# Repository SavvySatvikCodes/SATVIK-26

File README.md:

# SATVIK-26

**A custom STM32H743 flight controller, designed from scratch for ArduPilot.**

36 × 36 mm, 30.5 mm stack mounting, 4-layer. My first PCB, built for Hack Club Macondo.

---
## What this is

SATVIK-26 is a flight controller: the computer that reads a drone's sensors and decides how fast to spin each motor. It runs [ArduPilot](https://ardupilot.org/) on an STM32H743VIT6, a 480 MHz Cortex-M7.

Anyone can just buy a flight controller and assemble a drone, but I wanted to understand one. There is a large gap between knowing that an IMU talks over Serial Peripheral Interface contrast to having placed that IMU's decoupling capacitor yourself, knowing why it sits exactly where it sits. The only way I know to cross that gap is to draw the schematic and route the board.

This repo is the complete hardware design: schematic, layout, gerbers, BOM, and the reasoning behind the decisions.

---
## Specifications

- MCU - STM32H743VIT6, LQFP-100, 480 MHz Cortex-M7, 2 MB flash/1 MB RAM
- IMU	- ICM-42688-P (TDK InvenSense), SPI1
- Barometer - BMP388 (Bosch), I2C2
- Storage - microSD on SDMMC1 for onboard logging
- USB-C with USBLC6-2SC6 ESD protection, DFU accessible
- Input - 2 to 6S direct battery, SMBJ26A TVS clamp
- 5 V rail - TPS54560 buck, 15 µH inductor, SS56 catch diode
- 3.3 V rail - AP2112K-3.3 LDO from the 5 V rail
- Sensing - VBAT divider and ESC current sense into ADC1
- Motor outputs - 8 PWM channels
- Serial - 6 UARTs on JST-GH connectors
- Board - 36 × 36 mm, 4-layer FR4, 1.6 mm, 3 mm corner radius
- Mounting - 4 × M3 at 30.5 mm (standard FC stack)
- Components - 80 footprints, 55 top and 25 bottom
- Weight - 40 g

---
## What makes this not a copy

**Dual airframe, 8 PWM outputs.** Most 5-inch quad boards break out four motor outputs. I mapped eight timer channels to headers so the same board can fly a quad now and a fixed-wing later, where you need servo channels for ailerons, elevator and rudder on top of throttle. Four outputs would have made this a dead end. Eight cost me real routing space on a 36 mm board, and I decided the flexibility was worth it.

**FPV designed in, not bolted on.** A dedicated UART is broken out for a video transmitter, and the 5 V rail is sized with headroom to feed a camera and VTX rather than just flight electronics. Retrofitting FPV onto a board that never planned for it means splicing into power and hunting for a spare serial port.

**A custom ArduPilot hwdef.** ArduPilot does not know what is wired where on a board it has never seen. I am writing a `hwdef.dat` describing every peripheral, pin function and timer assignment, and the build system compiles firmware specifically for your hardware. That port is part of this project. The board is not finished until it boots real firmware.

For the record: Macondo's flight controller guide builds a **rocket** FC on a different MCU with a battery charger IC. This is a drone FC on an H7, no charger, different power tree, different sensors.

---
## Design decisions

- **TPS54560 buck, rated to 60V.** On 4S that looks like overkill, and cheaper 28 V parts would work. I took the headroom deliberately. 6S is 25.2 V charged, uncomfortably close to a 28 V absolute maximum, and a motor decelerating hard dumps energy back into the rail.
- **Entire power section moved to the back.** I could not route the board with everything on top. Rather than grow it to 40 × 40 and lose stack compatibility, the buck, inductor, LDO, filter caps and thirteen control passives all went to the bottom. That freed the top for MCU fanout, and it put the noisiest thing on the board on the opposite side of a solid ground plane from the IMU, crystal and USB pair. A space fix that turned out to be the right electrical call.
- **IMU as close to the mounting centroid as possible.** The further a sensor sits from the centre of rotation, the more frame vibration it reads as acceleration that is not real. Vibration is the most common cause of bad behaviour in custom ArduPilot builds.
- **Lower KV motors chosen on purpose.** 1855 KV instead of the common 2400 KV. Lower prop RPM means less vibration reaching an IMU sitting on a board I designed myself with no proven mounting. It is also more efficient, which buys flight time. 2400 KV would give roughly 9:1 thrust-to-weight, which is race-quad territory and pointless for a GPS platform flying Loiter and Auto. It also makes tuning the IMU harder.

---
## Stackup
Four layers: **F.Cu** signal, **In1.Cu** GND plane, **In2.Cu** +3V3 plane, **B.Cu** signal and power section.

+3V3 touches 38 pads spread across the whole board. The net that is everywhere gets the plane. VBAT_RAW became short traces, which is all a local 8-pad net needs.

---
## The work

The tidy version above is not how it felt.
Placing components looks like the easy part. It is not. Almost anything fits on a board if all you care about is fitting. I built layouts that passed every clearance check and were physically impossible to route, with pads jammed against the board edge and no path out at all. Each one had to be scrapped and rebuilt.

The final routing push ran **18 hours straight, 1pm on July 22nd to 6am on July 23rd, without a break.** By the end: 1114 track segments, 89 vias, zero unconnected pads.

Some NotSoFun blunders:
- The IMU had been deleted from the board entirely, and I had not noticed
- The crystal had been deleted too
- Thirteen buck and LDO support components stranded on the wrong side after the power flip, meaning a switching regulator's feedback network would have had to via across the board
- A netclass rule silently matching nothing, so every "power" trace was drawing at 0.2 mm instead of 0.6 mm

AND YES... after so much work it is quite nail-biting to put it on JLCPCB to see if your work actually computes... the real test is still far off 

---

## Things I got wrong

- **Connector pin order.** My connectors run 5V, GND, TX, RX. Most off-the-shelf GPS modules and telemetry radios use Pixhawk order with ground on the _last_ pin. Stock cables do not line up, and plugging one in without checking could push 5 V into a UART pin. Fixable by re-pinning cables, so the board still works as designed, but it is a genuine mistake and first on the rev 2 list. Every cable gets continuity-tested before it goes anywhere near power.
- **Thermal reliefs on the ground pours.** Ground connected to pads through four thin spokes, which exists to stop the plane wicking heat away during _hand_ soldering. On a dense board several pads could not fit the minimum spoke count. This board is reflow assembled, so thermal relief was simply the wrong setting. Switched to solid, which is better electrically and thermally.
- **Traces do not follow components.** Move a part after routing and the copper stays behind, silently disconnected. I found this out by doing it. Placement gets finished properly before routing starts.

---
## What I would do differently

- **Stop designing version one like it is the last version.** Most of my pain came from trying to make the first board complete instead of making it _work_. A first revision exists to prove the core design is sound and to teach you what you got wrong. Every extra feature is another thing that can be wrong, and another thing you have to route.
- **Smaller connectors.** JST-GH is the right professional choice and it is what real flight controllers use, but it is physically large and it ate a serious amount of board edge and routing space on a 36 mm board. On a first iteration I would take something more compact, or simply break out fewer UARTs.
- **Skip the gimmicks.** Status LEDs and their resistors, extra headers, nice-to-haves. None of them made the board work. All of them competed for space against things that did.
- **Plan the escape routes before finalizing placement.** The lesson that cost the most time. A component is not placed correctly just because it fits and clears its neighbours. It is placed correctly when every one of its pads has a realistic path to where it needs to go.

---
## Airframe and flight dynamics

| Item                        | Mass       |
| --------------------------- | ---------- |
| 5-inch carbon frame         | 120 g      |
| 4 × 2207 motors             | 132 g      |
| 4-in-1 ESC                  | 14 g       |
| SATVIK-26 FC                | 40 g       |
| GPS, compass, mast          | 18 g       |
| RC receiver                 | 15 g       |
| Telemetry radio (air)       | 15 g       |
| Propellers                  | 18 g       |
| Wiring, standoffs, hardware | 35 g       |
| **Dry**                     | **407 g**  |
| 4S 1850 mAh LiPo            | 244 g      |
| **All-up weight**           | **~651 g** |
|                             |            |
___
## Airframe parts

| Part            | Chosen component                    |
| --------------- | ----------------------------------- |
| Frame           | TBS Source One V6, 5 inch           |
| Motors          | iFlight XING2 2207 1855 KV (×4)     |
| ESC             | Sequre Blueson A2 6S 65A, AM32      |
| Propellers      | Gemfan 51466 tri-blade, 5 inch      |
| GPS and compass | Sequre M10-252Q with QMC5883        |
| Telemetry       | Micoair 915 MHz LoRa pair           |
| RC link         | FlySky FS-i6X with FS-iA6B receiver |
| Battery         | GNB 1850 mAh 4S 120C, XT60 (×2)     |
| FC mounting     | Rubber or TPU soft mounts           |
With XING2 2207 1855 KV motors on 4S: roughly **6.8:1 thrust-to-weight**, hover throttle around **38 %**, estimated **5-8 minutes** of mixed GPS flying.

---
## Status

- [x] Schematic complete, ERC clean
- [x] Component placement
- [x] 4-layer routing complete, 0 unconnected pads
- [x] DRC clean
- [x] Gerbers verified in JLCPCB's viewer
- [x] BOM and pick-and-place prepared
- [ ] Boards ordered
- [ ] ArduPilot `hwdef` written and firmware compiled
- [ ] Bring-up
- [ ] Airframe assembly
- [ ] Maiden hover
- [ ] Loiter and Auto missions

**Bring-up is planned in order:** visual inspection, then a current-limited bench supply with the limit set low, then every rail verified with a multimeter before a battery touches the board, then USB enumeration and DFU, then flash ArduPilot, then confirm each peripheral in Mission Planner one at a time. Motors tested with **propellers removed**.

---
## Regulatory
Over 250 g, so under Transport Canada rules this must be registered and flown by a certified pilot. That means you (& I) am taking the Small Basic Exam and registering the aircraft.

Basic certification allows uncontrolled (Class G) airspace only, 30 m from bystanders, below 400 ft, within visual line of sight. Most of Toronto is controlled airspace, which needs Advanced certification and a manufacturer safety-assurance declaration, something a homebuilt aircraft cannot obtain by definition. So fly out of city, many apps show you the proper zones.

---
## Tools

**[KiCad 10](https://www.kicad.org/)** for schematic and layout. **[STM32CubeMX](https://www.st.com/en/development-tools/stm32cubemx.html)** for pin mapping. [**ArduPilot**](https://ardupilot.org/) as target firmware, with SITL for development during parts lead time. **[JLCPCB](https://jlcpcb.com/)** for 4-layer fabrication and assembly.

---
CREDITS TO [OBSIDIAN](https://obsidian.md/), an .md file editor and notes taking app, for easing the process of writing in this file format.

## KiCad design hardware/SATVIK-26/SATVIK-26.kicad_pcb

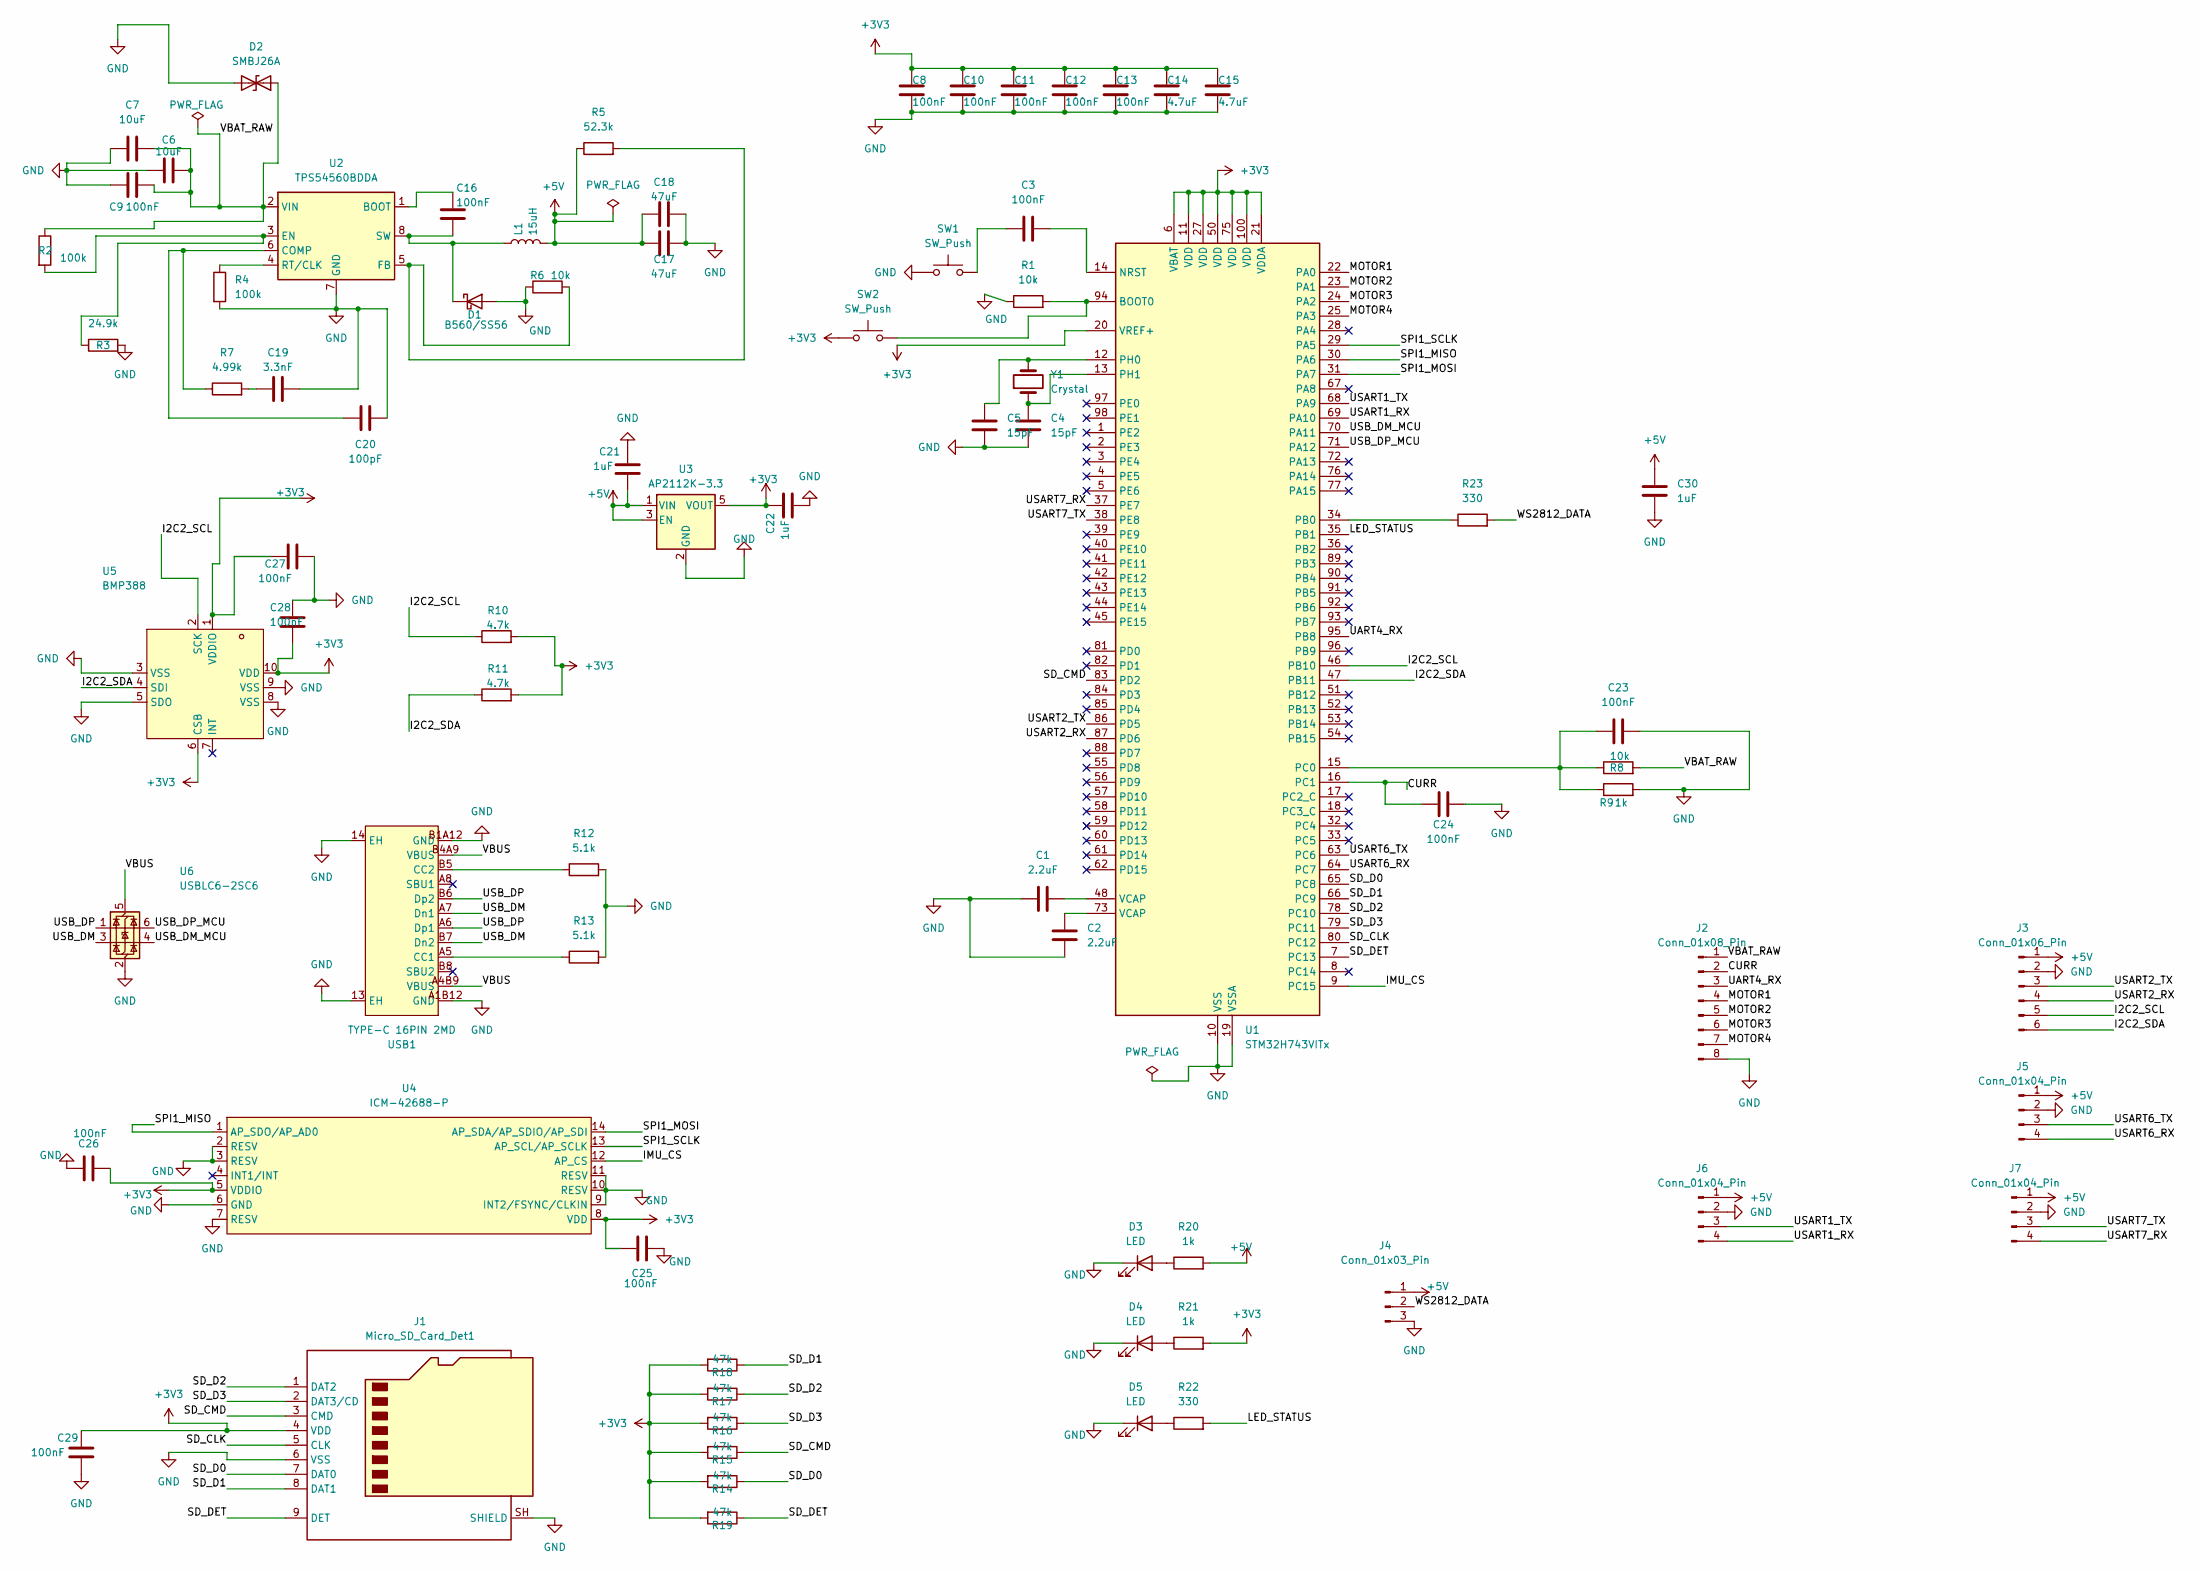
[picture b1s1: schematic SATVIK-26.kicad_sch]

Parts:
C1, C2: 2.2uF; C_0402_1005Metric
C3, C8, C9, C10, C11, C12, C13, C16, C23, C24, C25, C26, C27, C28, C29: 100nF; C_0402_1005Metric
C4, C5: 15pF; C_0402_1005Metric
C6, C7: 10uF; C_1206_3216Metric
C14, C15: 4.7uF; C_0603_1608Metric
C17, C18: 47uF; C_1206_3216Metric
C19: 3.3nF; C_0402_1005Metric
C20: 100pF; C_0402_1005Metric
C21, C22, C30: 1uF; C_0402_1005Metric
D1: B560/SS56; D_SMA
D2: SMBJ26A; D_SMB
D3, D4, D5: LED; LED_0603_1608Metric
J1: Micro_SD_Card_Det1; microSD_HC_Hirose_DM3AT-SF-PEJM5
J2: Conn_01x08_Pin; JST_GH_SM08B-GHS-TB_1x08-1MP_P1.25mm_Horizontal
J3: Conn_01x06_Pin; JST_GH_SM06B-GHS-TB_1x06-1MP_P1.25mm_Horizontal
J4: Conn_01x03_Pin; JST_GH_SM03B-GHS-TB_1x03-1MP_P1.25mm_Horizontal
J5, J6, J7: Conn_01x04_Pin; JST_GH_SM04B-GHS-TB_1x04-1MP_P1.25mm_Horizontal
L1: 15uH; IND-SMD_L10.4-W10.3
R1, R6, R8: 10k; R_0402_1005Metric
R2, R4: 100k; R_0402_1005Metric
R3: 24.9k; R_0402_1005Metric
R5: 52.3k; R_0402_1005Metric
R7: 4.99k; R_0402_1005Metric
R9, R20, R21: 1k; R_0402_1005Metric
R10, R11: 4.7k; R_0402_1005Metric
R12, R13: 5.1k; R_0402_1005Metric
R14, R15, R16, R17, R18, R19: 47k; R_0402_1005Metric
R22, R23: 330; R_0402_1005Metric
SW1, SW2: SW_Push; SW-SMD_4P-L5.1-W5.1-P3.70-LS6.5-TL_H1.5
U1: STM32H743VITx; LQFP-100_14x14mm_P0.5mm
U2: TPS54560BDDA; Texas_R-PDSO-G8_EP2.95x4.9mm_Mask2.4x3.1mm_ThermalVias
U3: AP2112K-3.3; SOT-23-5
U4: ICM-42688-P; LGA-14_L3.0-W2.5-P0.50-TL; MPN ICM-42688-P; LCSC Part C1850418
U5: BMP388; SENSORM-SMD_BMP388; MPN BMP388; LCSC Part C779278
U6: USBLC6-2SC6; SOT-23-6
USB1: TYPE-C 16PIN 2MD; USB-C-SMD_TYPE-C-16PIN-2MD-073; MPN TYPE-C 16PIN 2MD(073); LCSC Part C2765186
Y1: Crystal; CRYSTAL-SMD_4P-L3.2-W2.5-BL

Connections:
+3V3: C8.1, C10.1, C11.1, C12.1, C13.1, C14.1, C15.1, C22.1, C25.1, C26.1, C27.1, C28.2, C29.1, J1.4 (VDD), R10.2, R11.2, R14.2, R15.2, R16.2, R17.2, R18.2, R19.2, R21.2, SW2.1, U1.6 (VBAT), U1.11 (VDD), U1.20 (VREF+), U1.21 (VDDA), U1.27 (VDD), U1.50 (VDD), U1.75 (VDD), U1.100 (VDD), U3.5 (VOUT), U4.5 (VDDIO), U4.8 (VDD), U5.1 (VDDIO), U5.6 (CSB), U5.10 (VDD)
+5V: C17.1, C18.1, C21.2, C30.1, J3.1, J4.1, J5.1, J6.1, J7.1, L1.2, R5.1, R20.2, U3.1 (VIN), U3.3 (EN)
/CURR: C24.2, J2.2, U1.16 (PC1)
/I2C2_SCL: J3.5, R10.1, U1.46 (PB10), U5.2 (SCK)
/I2C2_SDA: J3.6, R11.1, U1.47 (PB11), U5.4 (SDI)
/IMU_CS: U1.9 (PC15), U4.12 (AP_CS)
/LED_STATUS: R22.2, U1.35 (PB1)
/MOTOR1: J2.4, U1.22 (PA0)
/MOTOR2: J2.5, U1.23 (PA1)
/MOTOR3: J2.6, U1.24 (PA2)
/MOTOR4: J2.7, U1.25 (PA3)
/SD_CLK: J1.5 (CLK), U1.80 (PC12)
/SD_CMD: J1.3 (CMD), R15.1, U1.83 (PD2)
/SD_D0: J1.7 (DAT0), R14.1, U1.65 (PC8)
/SD_D1: J1.8 (DAT1), R18.1, U1.66 (PC9)
/SD_D2: J1.1 (DAT2), R17.1, U1.78 (PC10)
/SD_D3: J1.2 (DAT3/CD), R16.1, U1.79 (PC11)
/SD_DET: J1.9 (DET), R19.1, U1.7 (PC13)
/SPI1_MISO: U1.30 (PA6), U4.1 (AP_SDO/AP_AD0)
/SPI1_MOSI: U1.31 (PA7), U4.14 (AP_SDA/AP_SDIO/AP_SDI)
/SPI1_SCLK: U1.29 (PA5), U4.13 (AP_SCL/AP_SCLK)
/UART4_RX: J2.3, U1.95 (PB8)
/USART1_RX: J6.4, U1.69 (PA10)
/USART1_TX: J6.3, U1.68 (PA9)
/USART2_RX: J3.4, U1.87 (PD6)
/USART2_TX: J3.3, U1.86 (PD5)
/USART6_RX: J5.4, U1.64 (PC7)
/USART6_TX: J5.3, U1.63 (PC6)
/USART7_RX: J7.4, U1.37 (PE7)
/USART7_TX: J7.3, U1.38 (PE8)
/USB_DM: U6.3 (I/O2), USB1.A7 (Dn1), USB1.B7 (Dn2)
/USB_DM_MCU: U1.70 (PA11), U6.4 (I/O2)
/USB_DP: U6.1 (I/O1), USB1.A6 (Dp1), USB1.B6 (Dp2)
/USB_DP_MCU: U1.71 (PA12), U6.6 (I/O1)
/VBAT_RAW: C6.2, C7.2, C9.2, D2.1 (A1), J2.1, R2.1, R8.2, U2.2 (VIN)
/VBUS: U6.5 (VBUS), USB1.A4B9 (VBUS), USB1.B4A9 (VBUS)
/WS2812_DATA: J4.2, R23.2
GND: C1.1, C2.2, C4.1, C5.1, C6.1, C7.1, C8.2, C9.1, C10.2, C11.2, C12.2, C13.2, C14.2, C15.2, C17.2, C18.2, C19.2, C20.2, C21.1, C22.2, C23.2, C24.1, C25.2, C26.2, C27.2, C28.1, C29.2, C30.2, D1.2 (A), D2.2 (A2), D3.1 (K), D4.1 (K), D5.1 (K), J1.6 (VSS), J1.SH (SHIELD), J2.8, J3.2, J4.3, J5.2, J6.2, J7.2, R1.1, R3.2, R4.2, R6.1, R9.2, R12.2, R13.2, SW1.1, U1.10 (VSS), U1.19 (VSSA), U1.26 (VSS), U1.49 (VSS), U1.74 (VSS), U1.99 (VSS), U2.7 (GND), U2.9 (GND), U3.2 (GND), U4.2 (RESV), U4.3 (RESV), U4.6 (GND), U4.7 (RESV), U4.9 (INT2/FSYNC/CLKIN), U4.10 (RESV), U4.11 (RESV), U5.3 (VSS), U5.5 (SDO), U5.8 (VSS), U5.9 (VSS), U6.2 (GND), USB1.13 (EH), USB1.14 (EH), USB1.A1B12 (GND), USB1.B1A12 (GND)
unnamed: C1.2, U1.48 (VCAP)
unnamed: C2.1, U1.73 (VCAP)
unnamed: C3.1, SW1.2
unnamed: C19.1, R7.2
unnamed: C16.2, D1.1 (K), L1.1, U2.8 (SW)
unnamed: D3.2 (A), R20.1
unnamed: D4.2 (A), R21.1
unnamed: D5.2 (A), R22.1
unnamed: R1.2, SW2.2, U1.94 (BOOT0)
unnamed: C3.2, U1.14 (NRST)
unnamed: R23.1, U1.34 (PB0)
unnamed: C23.1, R8.1, R9.1, U1.15 (PC0)
unnamed: C5.2, U1.12 (PH0), Y1.2
unnamed: C4.2, U1.13 (PH1), Y1.1
unnamed: C16.1, U2.1 (BOOT)
unnamed: C20.1, R7.1, U2.6 (COMP)
unnamed: R2.2, R3.1, U2.3 (EN)
unnamed: R5.2, R6.2, U2.5 (FB)
unnamed: R4.1, U2.4 (RT/CLK)
unnamed: R13.1, USB1.A5 (CC1)
unnamed: R12.1, USB1.B5 (CC2)

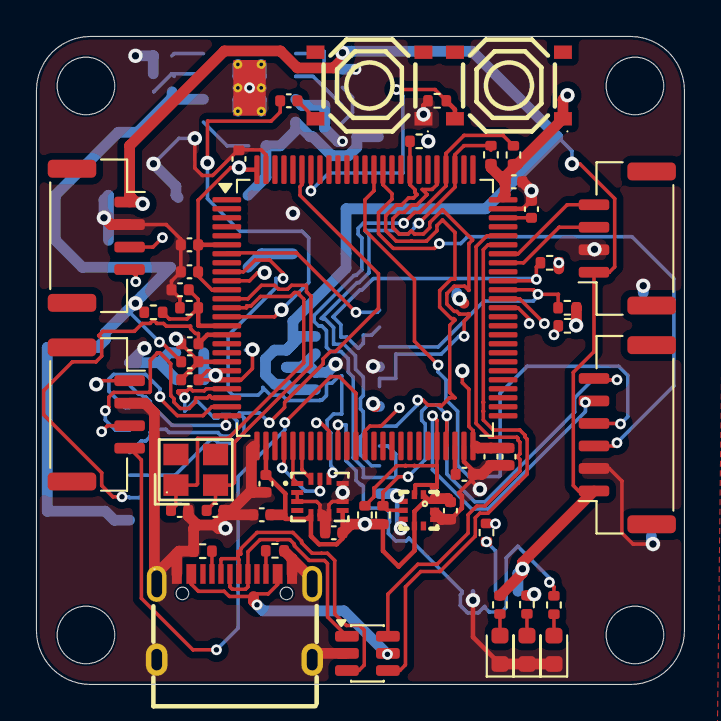
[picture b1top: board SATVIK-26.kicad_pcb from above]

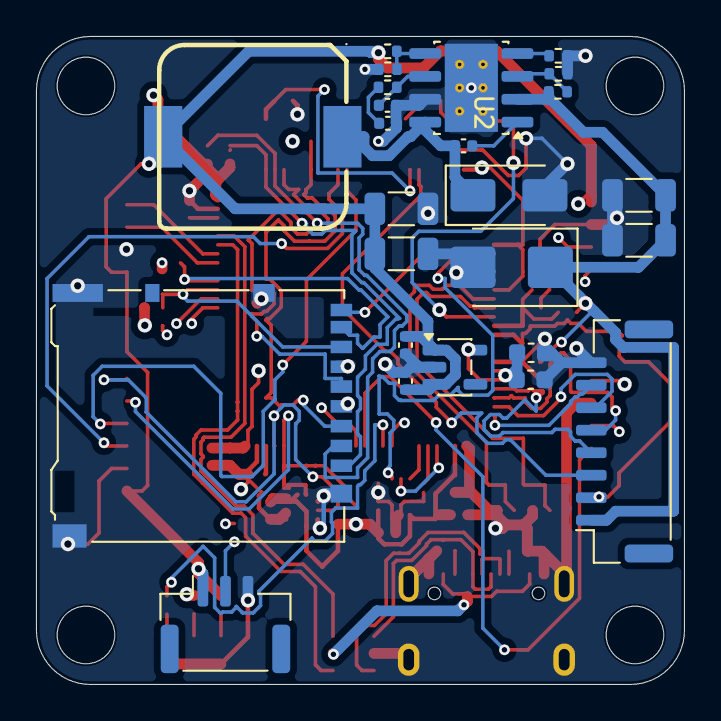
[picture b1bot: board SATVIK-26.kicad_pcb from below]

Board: 4 copper layers, 36.0 x 36.0 mm, 76 parts (25 on the bottom side), 59 nets.

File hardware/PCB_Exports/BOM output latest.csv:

Comment,Designator,Footprint,JLCPCB Part #（optional）
2.2uF,"C1,C2",0402,C12530
100nF,"C3,C8,C9,C10,C11,C12,C13,C16,C23,C24,C25,C26,C27,C28,C29",0402,C1525
15pF,"C4,C5",0402,C1548
10uF,"C6,C7",1206,C13585
4.7uF,"C14,C15",0603,C19666
47uF,"C17,C18",1206,C96123
3.3nF,C19,0402,C26404
100pF,C20,0402,C1546
1uF,"C21,C22,C30",0402,C52923
SS56,D1,SMA,C65009
SMBJ26A,D2,SMB,C3019963
LED white,"D3,D4,D5",0603,C2290
DM3AT-SF-PEJM5,J1,microSD_HC_Hirose_DM3AT-SF-PEJM5,
SM08B-GHS-TB,J2,JST_GH_SM08B-GHS-TB_1x08-1MP_P1.25mm_Horizontal,
SM06B-GHS-TB,J3,JST_GH_SM06B-GHS-TB_1x06-1MP_P1.25mm_Horizontal,
SM03B-GHS-TB,J4,JST_GH_SM03B-GHS-TB_1x03-1MP_P1.25mm_Horizontal,
SM04B-GHS-TB,"J5,J6,J7",JST_GH_SM04B-GHS-TB_1x04-1MP_P1.25mm_Horizontal,
15uH,L1,"SMD,10.4x10.3mm",C16113
10k,"R1,R6,R8",0402,C25744
100k,"R2,R4",0402,C25741
24.9k,R3,0402,C25874
52.3k,R5,0402,C26982
4.99k,R7,0402,C25903
1k,"R9,R20,R21",0402,C11702
4.7k,"R10,R11",0402,C25900
5.1k,"R12,R13",0402,C25905
47k,"R14,R15,R16,R17,R18,R19",0402,C25792
330,"R22,R23",0402,C25104
TS-1187A-B-A-B,"SW1,SW2",SW-SMD_4P-L5.1-W5.1-P3.70-LS6.5-TL_H1.5,C318884
STM32H743VIT6,U1,LQFP-100,C114409
TPS54560BDDA,U2,SOIC-8-EP,C31966
AP2112K-3.3,U3,SOT-23-5,C51118
ICM-42688-P,U4,LGA-14,C1850418
BMP388,U5,LGA-10,C779278
USBLC6-2SC6,U6,SOT-23-6,C2827654
TYPE-C 16PIN 2MD,USB1,USB-C-SMD_TYPE-C-16PIN-2MD-073,C2765186
8MHz,Y1,SMD3225-4P,C2682775

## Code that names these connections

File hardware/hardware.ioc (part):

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Mcu.Name=STM32H743VITx
Mcu.Package=LQFP100
Mcu.UserName=STM32H743VITx
PA0.Signal=S_TIM5_CH1
PA1.Signal=S_TIM5_CH2
PA10.Mode=Asynchronous
PA10.Signal=USART1_RX
PA11.Mode=Device_Only
PA11.Signal=USB_OTG_FS_DM
PA12.Mode=Device_Only
PA12.Signal=USB_OTG_FS_DP
PA13\ (JTMS/SWDIO).Signal=DEBUG_JTMS-SWDIO
PA14\ (JTCK/SWCLK).Signal=DEBUG_JTCK-SWCLK
PA2.Signal=S_TIM5_CH3
PA3.Signal=S_TIM5_CH4
PA5.Mode=Full_Duplex_Master
PA5.Signal=SPI1_SCK
PA6.Mode=Full_Duplex_Master
PA6.Signal=SPI1_MISO
PA7.Mode=Full_Duplex_Master
PA7.Signal=SPI1_MOSI
PA9.Mode=Asynchronous
PA9.Signal=USART1_TX
PB0.Signal=S_TIM3_CH3
PB1.Signal=S_TIM3_CH4
PB10.Mode=I2C
PB10.Signal=I2C2_SCL
PB11.Mode=I2C
PB11.Signal=I2C2_SDA
PB8.Mode=Asynchronous
PB8.Signal=UART4_RX
PB9.Mode=Asynchronous
PB9.Signal=UART4_TX
PC0.Signal=ADCx_INP10
PC1.Signal=ADCx_INP11
PC10.Mode=SD_4_bits_Wide_bus
PC10.Signal=SDMMC1_D2
PC11.Mode=SD_4_bits_Wide_bus
PC11.Signal=SDMMC1_D3
PC12.Mode=SD_4_bits_Wide_bus
PC12.Signal=SDMMC1_CK
PC15-OSC32_OUT\ (OSC32_OUT).Signal=GPIO_Output
PC6.Mode=Asynchronous
PC6.Signal=USART6_TX
PC7.Mode=Asynchronous
PC7.Signal=USART6_RX
PC8.Mode=SD_4_bits_Wide_bus
PC8.Signal=SDMMC1_D0
PC9.Mode=SD_4_bits_Wide_bus
PC9.Signal=SDMMC1_D1
PD2.Mode=SD_4_bits_Wide_bus
PD2.Signal=SDMMC1_CMD
PD5.Mode=Asynchronous
PD5.Signal=USART2_TX
PD6.Mode=Asynchronous
PD6.Signal=USART2_RX
PE7.Mode=Asynchronous
PE7.Signal=UART7_RX
PE8.Mode=Asynchronous
PE8.Signal=UART7_TX
PH0-OSC_IN\ (PH0).Mode=HSE-External-Oscillator
PH0-OSC_IN\ (PH0).Signal=RCC_OSC_IN
PH1-OSC_OUT\ (PH1).Mode=HSE-External-Oscillator
PH1-OSC_OUT\ (PH1).Signal=RCC_OSC_OUT
RCC.HSE_VALUE=8000000
RCC.SYSCLKFreq_VALUE=480000000
RCC.SYSCLKSource=RCC_SYSCLKSOURCE_PLLCLK
board=custom
